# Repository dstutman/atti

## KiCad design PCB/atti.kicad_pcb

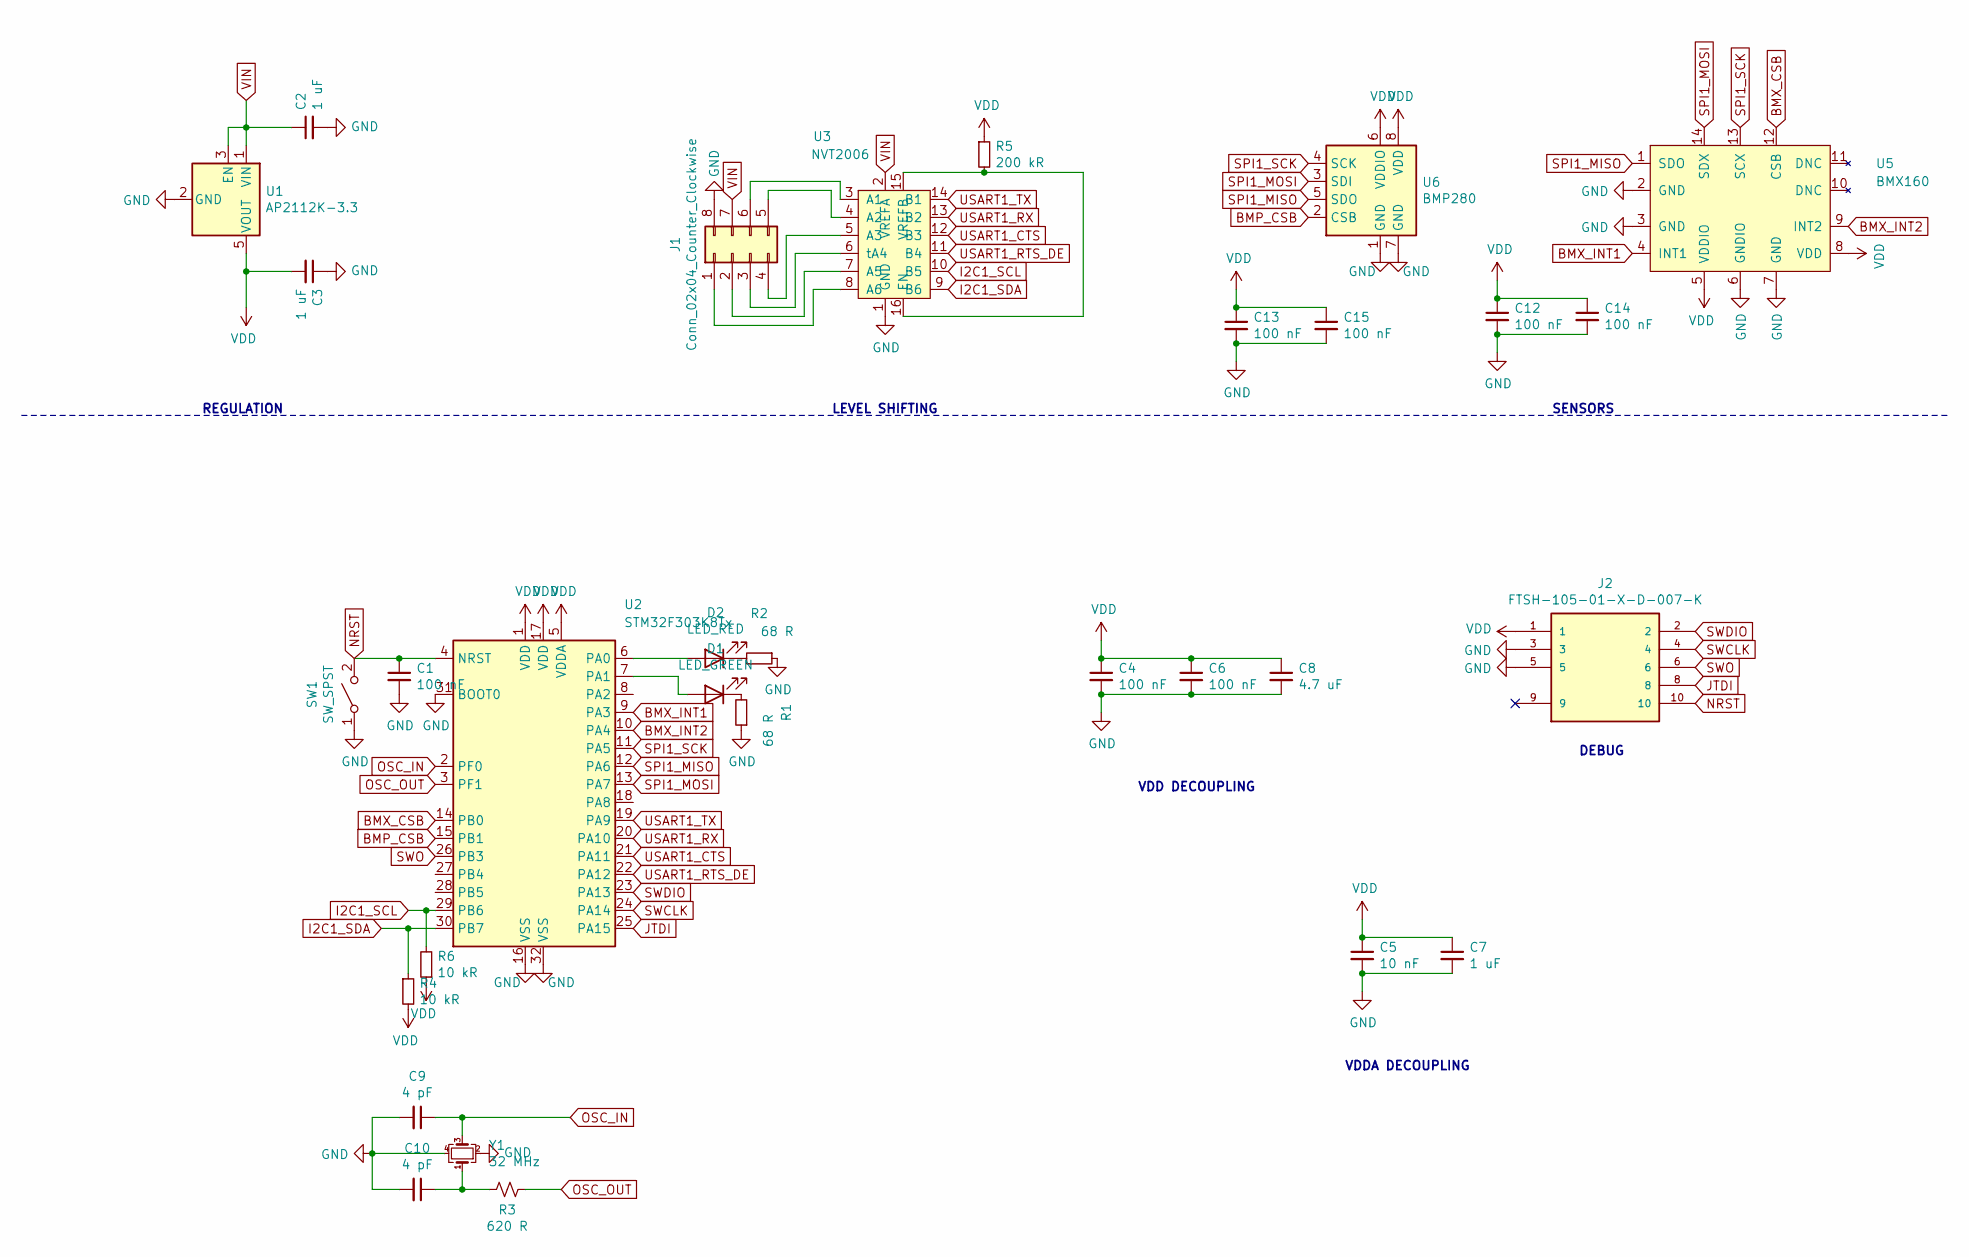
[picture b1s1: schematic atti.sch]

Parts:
C1, C4, C6, C12, C13, C14, C15: 100 nF; C_0805_2012Metric
C2, C3, C7: 1 uF; C_0805_2012Metric
C5: 10 nF; C_0805_2012Metric
C8: 4.7 uF; C_0805_2012Metric
C9, C10: 4 pF; C_0805_2012Metric
D1: LED_GREEN; LED_0805_2012Metric
D2: LED_RED; LED_0805_2012Metric
J1: Conn_02x04_Counter_Clockwise; PinHeader_2x04_P2.54mm_Vertical
J2: FTSH-105-01-X-D-007-K; SAMTEC_FTSH-105-01-X-D-007-K; PARTREV B
R1, R2: 68 R; R_0805_2012Metric
R3: 620 R; R_0805_2012Metric
R4, R6: 10 kR; R_0805_2012Metric
R5: 200 kR; R_0805_2012Metric
SW1: SW_SPST; SW_SPST_PTS810
U1: AP2112K-3.3; SOT-23-5
U2: STM32F303K8Tx; LQFP-32_7x7mm_P0.8mm
U3: NVT2006; TSSOP-16_4.4x5mm_P0.65mm
U5: BMX160; Bosch_LGA-14_3x2.5mm_P0.5mm
U6: BMP280; Bosch_LGA-8_2x2.5mm_P0.65mm_ClockwisePinNumbering
Y1: 32 MHz; Crystal_SMD_SeikoEpson_TSX3225-4Pin_3.2x2.5mm

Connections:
BMP_CSB: U2.15 (PB1), U6.2 (CSB)
BMX_CSB: U2.14 (PB0), U5.12 (CSB)
BMX_INT1: U2.9 (PA3), U5.4 (INT1)
BMX_INT2: U2.10 (PA4), U5.9 (INT2)
GND: C1.2, C2.2, C3.1, C4.2, C5.2, C6.2, C7.2, C8.2, C9.2, C10.2, C12.2, C13.2, C14.2, C15.2, J1.8, J2.3, J2.5, R1.1, R2.1, SW1.1 (A), U1.2 (GND), U2.16 (VSS), U2.31 (BOOT0), U2.32 (VSS), U3.1 (GND), U5.2 (GND), U5.3 (GND), U5.6 (GNDIO), U5.7 (GND), U6.1 (GND), U6.7 (GND), Y1.2, Y1.4
I2C1_SCL: R6.2, U2.29 (PB6), U3.10 (B5)
I2C1_SDA: R4.1, U2.30 (PB7), U3.9 (B6)
JTDI: J2.8, U2.25 (PA15)
NRST: C1.1, J2.10, SW1.2 (B), U2.4 (NRST)
unnamed: C10.1, R3.1, Y1.1
unnamed: D1.1 (K), R1.2
unnamed: D1.2 (A), U2.7 (PA1)
unnamed: D2.1 (K), R2.2
unnamed: D2.2 (A), U2.6 (PA0)
unnamed: J1.1, U3.8 (A6)
unnamed: J1.2, U3.7 (A5)
unnamed: J1.3, U3.6 (tA4)
unnamed: J1.4, U3.5 (A3)
unnamed: J1.5, U3.4 (A2)
unnamed: J1.6, U3.3 (A1)
unnamed: R5.2, U3.15 (VREFB), U3.16 (EN)
OSC_IN: C9.1, U2.2 (PF0), Y1.3
OSC_OUT: R3.2, U2.3 (PF1)
SPI1_MISO: U2.12 (PA6), U5.1 (SDO), U6.5 (SDO)
SPI1_MOSI: U2.13 (PA7), U5.14 (SDX), U6.3 (SDI)
SPI1_SCK: U2.11 (PA5), U5.13 (SCX), U6.4 (SCK)
SWCLK: J2.4, U2.24 (PA14)
SWDIO: J2.2, U2.23 (PA13)
SWO: J2.6, U2.26 (PB3)
USART1_CTS: U2.21 (PA11), U3.12 (B3)
USART1_RTS_DE: U2.22 (PA12), U3.11 (B4)
USART1_RX: U2.20 (PA10), U3.13 (B2)
USART1_TX: U2.19 (PA9), U3.14 (B1)
VDD: C3.2, C4.1, C5.1, C6.1, C7.1, C8.1, C12.1, C13.1, C14.1, C15.1, J2.1, R4.2, R5.1, R6.1, U1.5 (VOUT), U2.1 (VDD), U2.5 (VDDA), U2.17 (VDD), U5.5 (VDDIO), U5.8 (VDD), U6.6 (VDDIO), U6.8 (VDD)
VIN: C2.1, J1.7, U1.1 (VIN), U1.3 (EN), U3.2 (VREFA)

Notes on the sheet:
REGULATION
LEVEL SHIFTING
SENSORS
VDD DECOUPLING
VDDA DECOUPLING
DEBUG

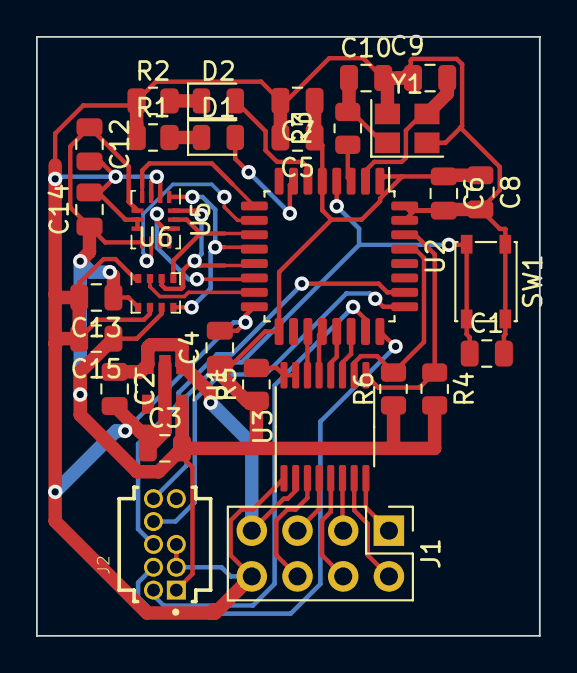
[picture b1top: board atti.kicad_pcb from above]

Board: 2 copper layers, 27.9 x 33.3 mm, 31 parts (0 on the bottom side), 35 nets.

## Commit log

2020-12-10 Setup and add major componentsThis adds the IMU, pressure sensor, microcontroller, and USB receptacle.
2020-12-12 Preliminary subdesign
2020-12-12 Add USB COM IC and various other routing work
2020-12-15 Finish preliminary schematic
2020-12-15 Partial routing attempt and programming connector
2020-12-16 Second routing attempt
2020-12-16 Good routing progress
2020-12-16 Routing complete

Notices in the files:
PCB/atti.sch:
Copyright Daniel Avishai Stutman, 2020
